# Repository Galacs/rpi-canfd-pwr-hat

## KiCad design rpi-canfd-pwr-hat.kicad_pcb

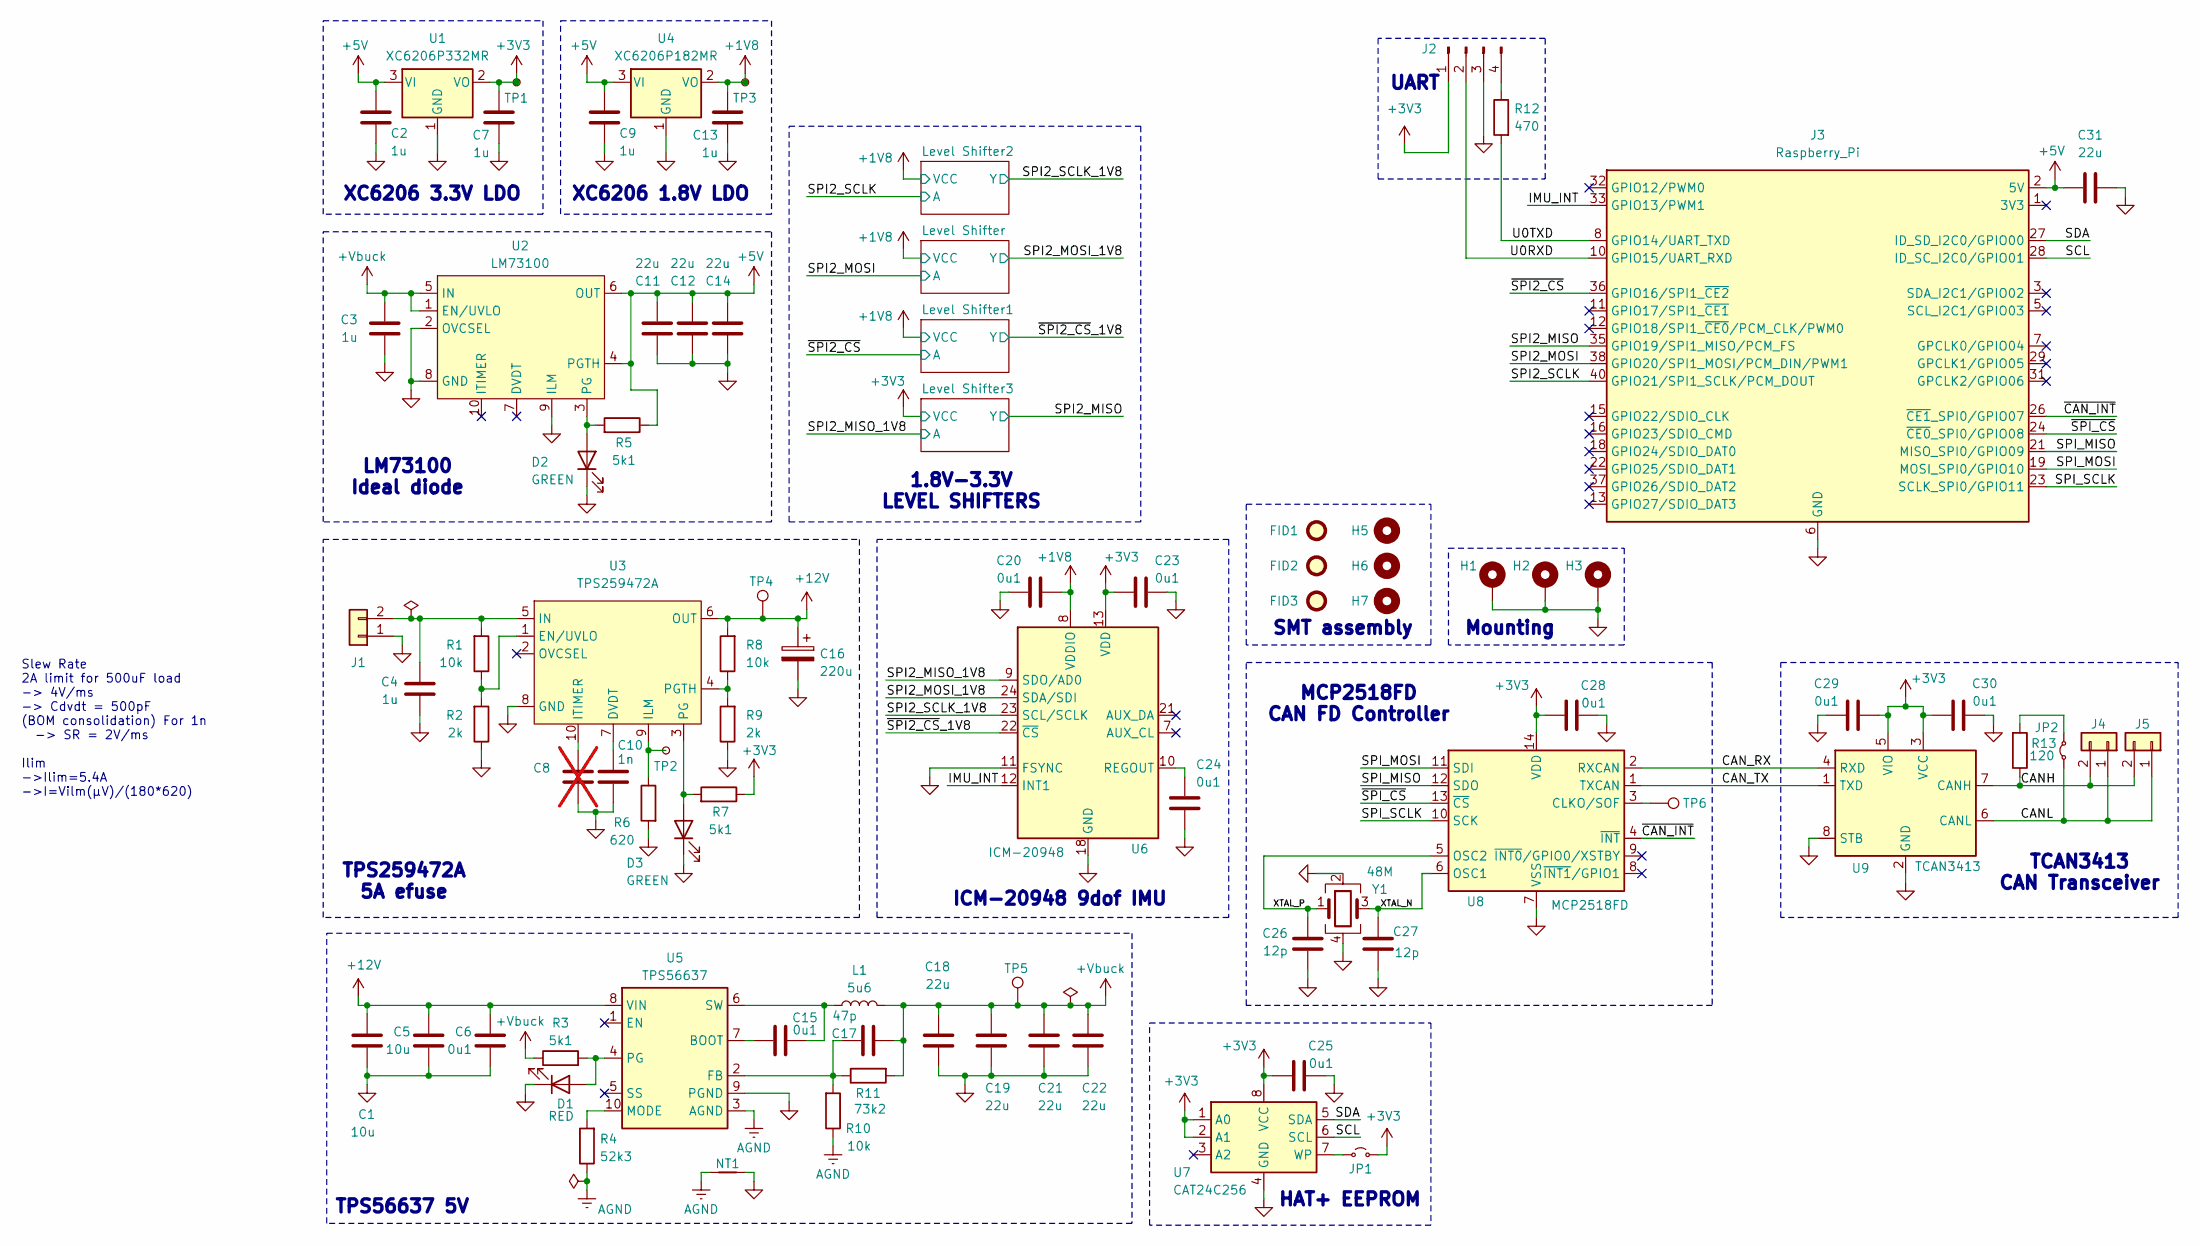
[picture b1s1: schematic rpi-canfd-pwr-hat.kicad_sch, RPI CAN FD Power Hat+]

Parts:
C1, C5: 10u; C_0805_2012Metric; Manufacturer Part Number GRM21BR61H106KE43L; JLCPCB Part # C440198
C2, C3, C4, C7, C9, C13: 1u; C_0402_1005Metric; Manufacturer Part Number CL05A105KA5NQNC; JLCPCB Part # C52923
C6, C15, C20, C23, C24, C25, C28, C29, C30: 0u1; C_0402_1005Metric; Manufacturer Part Number CL05B104KB54PNC; JLCPCB Part # C307331
C8: C; C_0402_1005Metric; not fitted
C10: 1n; C_0402_1005Metric; Manufacturer Part Number 0402B102K500NT; JLCPCB Part # C1523
C11, C12, C14, C18, C19, C21, C22, C31: 22u; C_0805_2012Metric; Manufacturer Part Number CL21A226MAQNNNE; JLCPCB Part # C45783
C16: 220u; CP_Elec_10x10.5; Manufacturer Part Number 50TZV220M10X10.5; JLCPCB Part # C88818
C17: 47p; C_0402_1005Metric; Manufacturer Part Number 0402CG470J500NT; JLCPCB Part # C1567
C26, C27: 12p; C_0402_1005Metric; Manufacturer Part Number 0402CG120J500NT; JLCPCB Part # C1547
D1: RED; LED_0603_1608Metric; Manufacturer Part Number KT-0603R; JLCPCB Part # C2286
D2, D3: GREEN; LED_0805_2012Metric; Manufacturer Part Number KT-0805G; JLCPCB Part # C2297
FID1, FID2, FID3: Fiducial; Fiducial_1mm_Mask2mm
H1, H2, H3: MountingHole_Pad; MountingHole_2.7mm_M2.5_Pad_Via
H5, H6, H7: MountingHole; ToolingHole_1.152mm
J1, J4, J5: Conn_01x02; JST_XH_B2B-XH-A_1x02_P2.50mm_Vertical; Manufacturer Part Number B2B-XH-A(LF)(SN); JLCPCB Part # C158012
J2: Conn_01x04_Pin; PinHeader_1x04_P2.54mm_Vertical
J3: Raspberry_Pi; PinSocket_2x20_P2.54mm_Vertical
JP1: Jumper_2_Small_Open; SolderJumper-2_P1.3mm_Open_RoundedPad1.0x1.5mm
JP2: Jumper_2_Small_Bridged; PinHeader_1x02_P2.54mm_Horizontal
L1: 5u6; L_Bourns_SRP1050WA; Manufacturer Part Number SMMS1050-5R6M; JLCPCB Part # C149541
NT1: NetTie_2; NetTie-2_SMD_Pad0.5mm
R1, R8, R10: 10k; R_0402_1005Metric; Manufacturer Part Number 0402WGF1002TCE; JLCPCB Part # C25744
R2, R9: 2k; R_0402_1005Metric; Manufacturer Part Number 0402WGF2001TCE; JLCPCB Part # C4109
R3, R5, R7: 5k1; R_0402_1005Metric; Manufacturer Part Number 0402WGF5101TCE; JLCPCB Part # C25905
R4: 52k3; R_0402_1005Metric; Manufacturer Part Number 0402WGF5232TCE; JLCPCB Part # C26982
R6: 620; R_0402_1005Metric; Manufacturer Part Number 0402WGF6200TCE; JLCPCB Part # C4961
R11: 73k2; R_0402_1005Metric; Manufacturer Part Number 0402WGF7322TCE; JLCPCB Part # C26986
R12: 470; R_0402_1005Metric; Manufacturer Part Number 0402WGF4700TCE; JLCPCB Part # C25117
R13: 120; R_1206_3216Metric; Manufacturer Part Number 1206W4F1200T5E; JLCPCB Part # C17909
TP1, TP2, TP3: TestPoint_Small; TestPoint_Pad_D2.0mm
TP4, TP5, TP6: TestPoint; TestPoint_Pad_D2.0mm
U1: XC6206P332MR; SOT-23-3; Manufacturer Part Number XC6206P332MR-G; JLCPCB Part # C5446
U2: LM73100; Texas_RPW0010A_VQFN-HR-10_2x2mm_P0.5mm; Manufacturer Part Number LM73100RPWR; JLCPCB Part # C3210761
U3: TPS259472A; Texas_RPW0010A_VQFN-HR-10_2x2mm_P0.5mm; Manufacturer Part Number TPS259472ARPWR; JLCPCB Part # C3662789
U4: XC6206P182MR; SOT-23-3; Manufacturer Part Number XC6206P182MR; JLCPCB Part # C347373
U5: TPS56637; Texas_RPA0010A_VQFN-HR-10_3x3mm_P0.5mm; Manufacturer Part Number TPS56637RPAR; JLCPCB Part # C841386
U6: ICM-20948; InvenSense_QFN-24_3x3mm_P0.4mm; Manufacturer Part Number ICM-20948; JLCPCB Part # C726001
U7: CAT24C256; SOIC-8_3.9x4.9mm_P1.27mm; Manufacturer Part Number CAT24C256WI-GT3; JLCPCB Part # C79987
U8: MCP2518FD; DFN-14-1EP_3x4.5mm_P0.65mm_EP1.65x4.25mm; Manufacturer Part Number MCP2518FDT-E/QBB; JLCPCB Part # C621395
U9: TCAN3413; TSOT-23-8; Manufacturer Part Number TCAN3413DDFR; JLCPCB Part # C30111221
Y1: 48M; Crystal_SMD_2016-4Pin_2.0x1.6mm; Manufacturer Part Number R940000096; JLCPCB Part # C7206306

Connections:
+1V8: C13.2, C20.1, TP3.1 (1_1), U4.2 (VO), U6.8 (VDDIO); also elsewhere on the board
+3V3: C7.2, C23.1, C25.1, C28.1, C29.1, C30.1, J2.1, JP1.2 (B), R7.1, TP1.1 (1_1), U1.2 (VO), U6.13 (VDD), U7.1 (A0), U7.2 (A1), U7.8 (VCC), U8.14 (VDD), U9.3 (VCC), U9.5 (VIO); also elsewhere on the board
+5V: C2.2, C9.2, C11.2, C12.2, C14.2, C31.1, J3.2 (5V), J3.4 (5V), R5.1, U1.3 (VI), U2.4 (PGTH), U2.6 (OUT), U4.3 (VI)
+12V: C1.1, C5.1, C6.1, C16.1, R8.2, TP4.1 (1_1), U3.6 (OUT), U5.8 (VIN)
+Vbuck: C3.2, C17.2, C18.1, C19.1, C21.1, C22.1, L1.2, R3.1, R11.2, TP5.1 (1_1), U2.1 (EN/UVLO), U2.5 (IN)
/CANH: J4.2, J5.2, R13.1, U9.7 (CANH)
/CANL: J4.1, J5.1, JP2.1 (A), U9.6 (CANL)
/CAN_RX: U8.2 (RXCAN), U9.4 (RXD)
/CAN_TX: U8.1 (TXCAN), U9.1 (TXD)
/IMU_INT: J3.33 (GPIO13/PWM1), U6.12 (INT1)
/SCL: J3.28 (ID_SC_I2C0/GPIO01), U7.6 (SCL)
/SDA: J3.27 (ID_SD_I2C0/GPIO00), U7.5 (SDA)
/SPI2_MISO: J3.35 (GPIO19/SPI1_MISO/PCM_FS); also elsewhere on the board
/SPI2_MISO_1V8: U6.9 (SDO/AD0); also elsewhere on the board
/SPI2_MOSI: J3.38 (GPIO20/SPI1_MOSI/PCM_DIN/PWM1); also elsewhere on the board
/SPI2_MOSI_1V8: U6.24 (SDA/SDI); also elsewhere on the board
/SPI2_SCLK: J3.40 (GPIO21/SPI1_SCLK/PCM_DOUT); also elsewhere on the board
/SPI2_SCLK_1V8: U6.23 (SCL/SCLK); also elsewhere on the board
/SPI_MISO: J3.21 (MISO_SPI0/GPIO09), U8.12 (SDO)
/SPI_MOSI: J3.19 (MOSI_SPI0/GPIO10), U8.11 (SDI)
/SPI_SCLK: J3.23 (SCLK_SPI0/GPIO11), U8.10 (SCK)
/U0RXD: J2.2, J3.10 (GPIO15/UART_RXD)
/U0TXD: J3.8 (GPIO14/UART_TXD), R12.2
/XTAL_N: C27.1, U8.6 (OSC1), Y1.3
/XTAL_P: C26.2, U8.5 (OSC2), Y1.1
/~CAN_INT: J3.26 (~CE1_SPI0/GPIO07), U8.4 (~INT)
/~SPI2_CS: J3.36 (GPIO16/SPI1_~CE2); also elsewhere on the board
/~SPI2_CS_1V8: U6.22 (~CS); also elsewhere on the board
/~SPI_CS: J3.24 (~CE0_SPI0/GPIO08), U8.13 (~CS)
AGND: NT1.1, R4.1, R10.1, U5.3 (AGND)
GND: C1.2, C2.1, C3.1, C4.1, C5.2, C6.2, C7.1, C8.2, C9.1, C10.2, C11.1, C12.1, C13.1, C14.1, C16.2, C18.2, C19.2, C20.2, C21.2, C22.2, C23.2, C24.2, C25.2, C26.1, C27.2, C28.2, C29.2, C30.2, C31.2, D1.1 (K), D2.1 (K), D3.1 (K), H1.1 (1_1), H2.1 (1_1), H3.1 (1_1), J1.1, J2.3, J3.6 (GND), J3.9 (GND), J3.14 (GND), J3.20 (GND), J3.25 (GND), J3.30 (GND), J3.34 (GND), J3.39 (GND), NT1.2, R2.1, R6.2, R9.1, U1.1 (GND), U2.2 (OVCSEL), U2.8 (GND), U2.9 (ILM), U3.8 (GND), U4.1 (GND), U5.9 (PGND), U6.11 (FSYNC), U6.18 (GND), U6.20 (GND), U7.4 (GND), U8.7 (VSS), U8.15 (VSS), U9.2 (GND), U9.8 (STB), Y1.2, Y1.4; also elsewhere on the board
unnamed: D1.2 (A), R3.2, U5.4 (PG)
unnamed: D2.2 (A), R5.2, U2.3 (PG)
unnamed: D3.2 (A), R7.2, U3.3 (PG)
unnamed: C4.2, J1.2, R1.2, U3.5 (IN)
unnamed: J2.4, R12.1
unnamed: JP1.1 (A), U7.7 (WP)
unnamed: JP2.2 (B), R13.2
unnamed: C10.1, U3.7 (DVDT)
unnamed: R1.1, R2.2, U3.1 (EN/UVLO)
unnamed: R6.1, TP2.1 (1_1), U3.9 (ILM)
unnamed: C8.1, U3.10 (ITIMER)
unnamed: R8.1, R9.2, U3.4 (PGTH)
unnamed: C15.1, U5.7 (BOOT)
unnamed: C17.1, R10.2, R11.1, U5.2 (FB)
unnamed: R4.2, U5.10 (MODE)
unnamed: C15.2, L1.1, U5.6 (SW)
unnamed: C24.1, U6.10 (REGOUT)
unnamed: TP6.1 (1_1), U8.3 (CLKO/SOF)

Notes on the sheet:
1.8V-3.3V LEVEL SHIFTERS
HAT+ EEPROM
Mounting
XC6206 1.8V LDO
TCAN3413 CAN Transceiver
Slew Rate 2A limit for 500uF load -> 4V/ms -> Cdvdt = 500pF (BOM consolidation) For 1n -> SR = 2V/ms Ilim ->Ilim=5.4A ->I=Vilm(µV)/(180*620)
LM73100 Ideal diode
XC6206 3.3V LDO
UART
TPS259472A 5A efuse
MCP2518FD CAN FD Controller
TPS56637 5V
ICM-20948 9dof IMU
SMT assembly

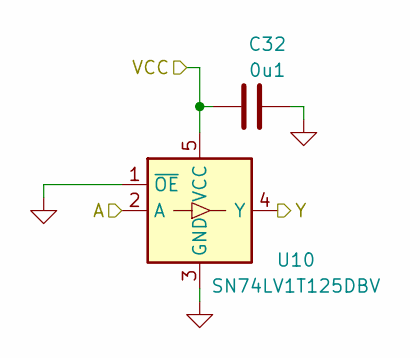
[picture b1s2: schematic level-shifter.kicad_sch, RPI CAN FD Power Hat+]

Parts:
C32: 0u1; C_0402_1005Metric; Manufacturer Part Number CL05B104KB54PNC; JLCPCB Part # C307331
U10: SN74LV1T125DBV; SOT-23-5; Manufacturer Part Number SN74LV1T125DBVR; JLCPCB Part # C473338

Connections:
+1V8: C32.1, U10.5 (VCC); also elsewhere on the board
/SPI2_MOSI: U10.2 (A); also elsewhere on the board
/SPI2_MOSI_1V8: U10.4 (Y); also elsewhere on the board
GND: C32.2, U10.1 (~OE), U10.3 (GND); also elsewhere on the board

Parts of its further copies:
C33, C34, C35: 0u1; C_0402_1005Metric; Manufacturer Part Number CL05B104KB54PNC; JLCPCB Part # C307331
U11, U12, U13: SN74LV1T125DBV; SOT-23-5; Manufacturer Part Number SN74LV1T125DBVR; JLCPCB Part # C473338

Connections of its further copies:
+1V8: C33.1, C34.1, U11.5 (VCC), U12.5 (VCC); also elsewhere on the board
+3V3: C35.1, U13.5 (VCC); also elsewhere on the board
/SPI2_MISO: U13.4 (Y); also elsewhere on the board
/SPI2_MISO_1V8: U13.2 (A); also elsewhere on the board
/SPI2_SCLK: U12.2 (A); also elsewhere on the board
/SPI2_SCLK_1V8: U12.4 (Y); also elsewhere on the board
/~SPI2_CS: U11.2 (A); also elsewhere on the board
/~SPI2_CS_1V8: U11.4 (Y); also elsewhere on the board
GND: C33.2, C34.2, C35.2, U11.1 (~OE), U11.3 (GND), U12.1 (~OE), U12.3 (GND), U13.1 (~OE), U13.3 (GND); also elsewhere on the board

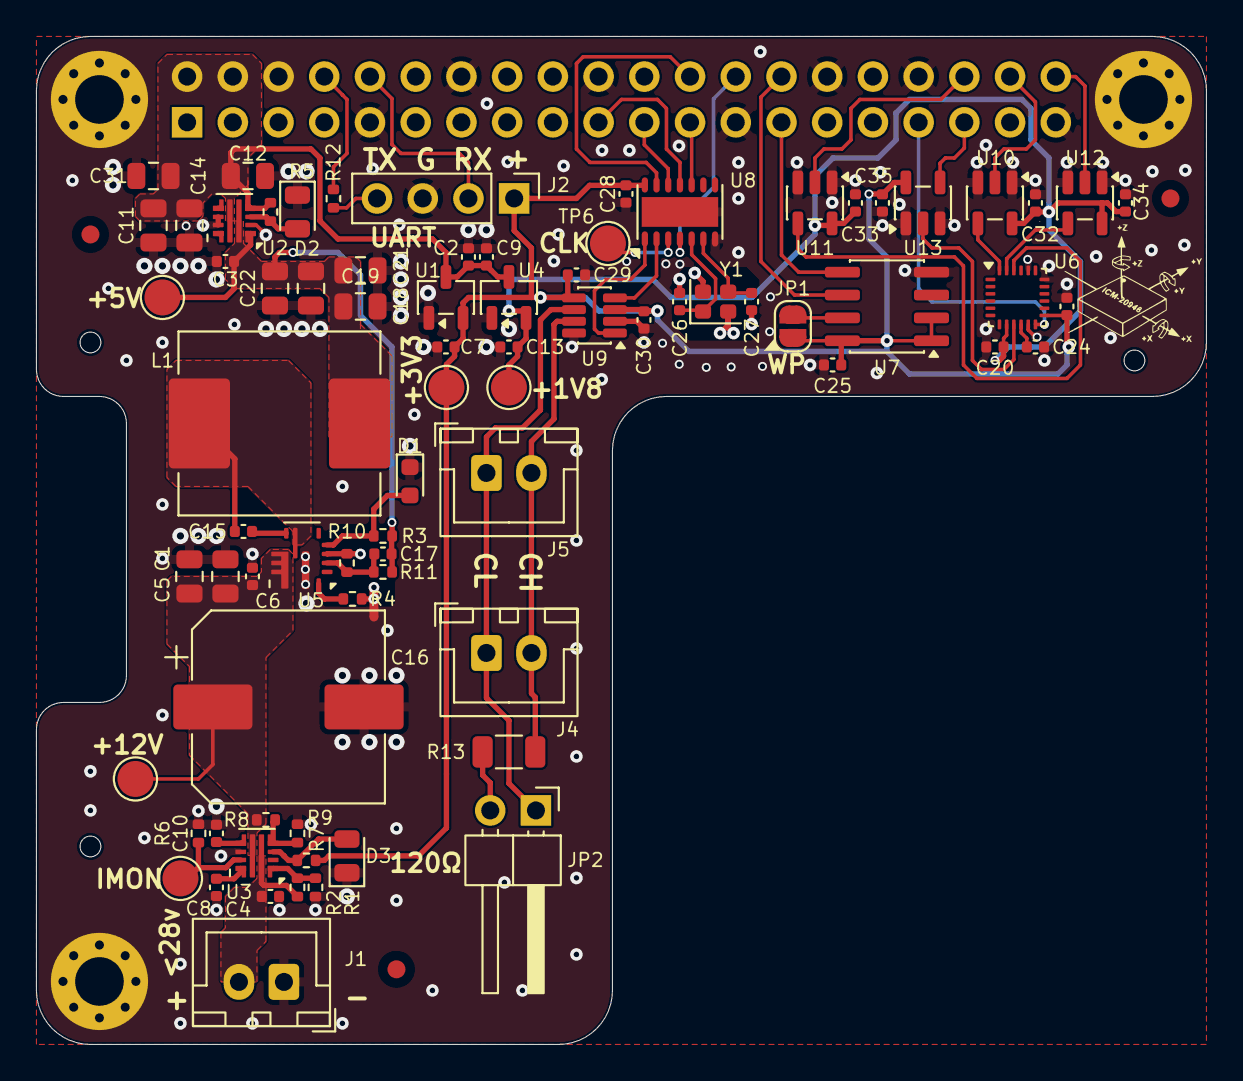
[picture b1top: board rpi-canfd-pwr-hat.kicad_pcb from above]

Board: 4 copper layers, 65.0 x 56.0 mm, 89 parts (1 on the bottom side), 49 nets.

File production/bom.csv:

Designator,Footprint,Quantity,Value,LCSC Part #
"C1, C5",0805,2,10u,C440198
C10,0402,1,1n,C1523
"C11, C12, C14, C18, C19, C21, C22, C31",0805,8,22u,C45783
"C13, C2, C3, C4, C7, C9",0402,6,1u,C52923
"C15, C20, C23, C24, C25, C28, C29, C30, C32, C33, C34, C35, C6",0402,13,0u1,C307331
C16,CP_Elec_6.3x7.7,1,220u,C2918361
C17,0402,1,47p,C1567
"C26, C27",0402,2,12p,C1547
D1,0603,1,RED,C2286
"D2, D3",0805,2,GREEN,C2297
L1,L_Bourns_SRP1050WA,1,5u6,C149541
"R1, R10, R8",0402,3,10k,C25744
R11,0402,1,73k2,C26986
R12,0402,1,470,C25117
R13,1206,1,120,C17909
"R2, R9",0402,2,2k,C4109
"R3, R5, R7",0402,3,5k1,C25905
R4,0402,1,52k3,C26982
R6,0402,1,620,C4961
U1,SOT-23-3,1,XC6206P332MR,C5446
"U10, U11, U12, U13",SOT-23-5,4,SN74LV1T125DBV,C473338
U2,Texas_RPW0010A_VQFN-HR-10_2x2mm_P0.5mm,1,LM73100,C3210761
U3,Texas_RPW0010A_VQFN-HR-10_2x2mm_P0.5mm,1,TPS259472A,C3662789
U4,SOT-23-3,1,XC6206P182MR,C347373
U5,Texas_RPA0010A_VQFN-HR-10_3x3mm_P0.5mm,1,TPS56637,C841386
U6,InvenSense_QFN-24_3x3mm_P0.4mm,1,ICM-20948,C726001
U7,SOIC-8_3.9x4.9mm_P1.27mm,1,CAT24C256,C79987
U8,DFN-14-1EP_3x4.5mm_P0.65mm_EP1.65x4.25mm,1,MCP2518FD,C621395
U9,TSOT-23-8,1,TCAN3413,C30111221
Y1,Crystal_SMD_2016-4Pin_2.0x1.6mm,1,48M,C7206306

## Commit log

2026-06-27 schem: add eeprom power hat+
2026-06-27 schem: add uart connector
2026-06-27 schem: add TPS56637 5v buck converter
2026-06-27 schem: add LM73100 Ideal diode
2026-06-27 schem: add TPS259472A 5A efuse
2026-06-27 schem: fix ufuse uvlo and pgth
2026-06-27 schem: remove i2c pullups
2026-06-27 schem: add MCP2518FD CAN FD Controller
2026-06-27 schem: add TCAN3413 CAN Transceiver
2026-06-28 schem: add ICM-20948 9dof IMU and level shifters
2026-06-28 schem: add XC6206 3.3V LDO
2026-06-28 schem: add XC6206 1.8V LDO
2026-06-28 schem: update TPS56637 datasheet
2026-06-28 schem: add no connects
2026-06-28 schem: run and fix ERC
2026-06-28 schem: add net classes
2026-06-28 schem: assign missing footprints
2026-06-28 schem: add ordering info to BOM
2026-06-28 schem: add title
2026-06-28 schem: renumber
2026-06-28 pcb: import jlc 4 layer stackup
2026-06-28 pcb: import components from schem
2026-06-28 pcb: add missing 3d models
2026-06-28 pcb: initial sectionning
2026-06-28 schem: add smt fiducials and tooling holes
2026-06-28 schem: add hat mounting holes
2026-06-28 pcb: add hat outline
2026-06-28 pcb: add can layout
2026-06-28 pcb: add imu layout
2026-06-28 pcb: add eeprom routing
2026-06-28 pcb: add smps layout
2026-06-28 pcb: add smps zone
2026-06-28 pcb: add input efuse routing
2026-06-28 pcb: update board outline
2026-06-28 pcb: final board layout
2026-06-28 pcb: add gnd planes
2026-06-28 pcb: add gnd vias
2026-06-28 pcb: add drill/place origin
2026-06-28 pcb: add xtal routing
2026-06-28 pcb: route imu
2026-06-28 pcb: route eeprom
2026-06-28 pcb: route input efuse
2026-06-28 pcb: route rpi power path
2026-06-28 pcb: route uart
2026-06-28 pcb: route ldos
2026-06-28 pcb: route can
2026-06-28 pcb: route +1v8 pwr
2026-06-28 pcb: add stitching vias
2026-06-28 pcb: run and fix DRC
2026-06-28 pcb: remove unuse dinternal pads
2026-06-28 pcb(silk): clean reference designators
2026-06-28 pcb(silk): add usr txt
2026-06-28 pcb: add title
2026-06-28 generate production files
2026-06-29 schem/pcb: switch to phat rubycon cap
2026-06-30 regenerate production files
